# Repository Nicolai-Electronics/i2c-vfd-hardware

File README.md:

# I2C controlled HCS-12SS59T VFD

This repository contains the hardware desgin files for the I2C controlled NE-HCS12SS59T-R01 Vacuum Fluorescent Display board.

## License

Copyright 2024 Nicolai Electronics

This hardware design may be used under the terms of the [CERN-OHL-P](LICENSE) license.

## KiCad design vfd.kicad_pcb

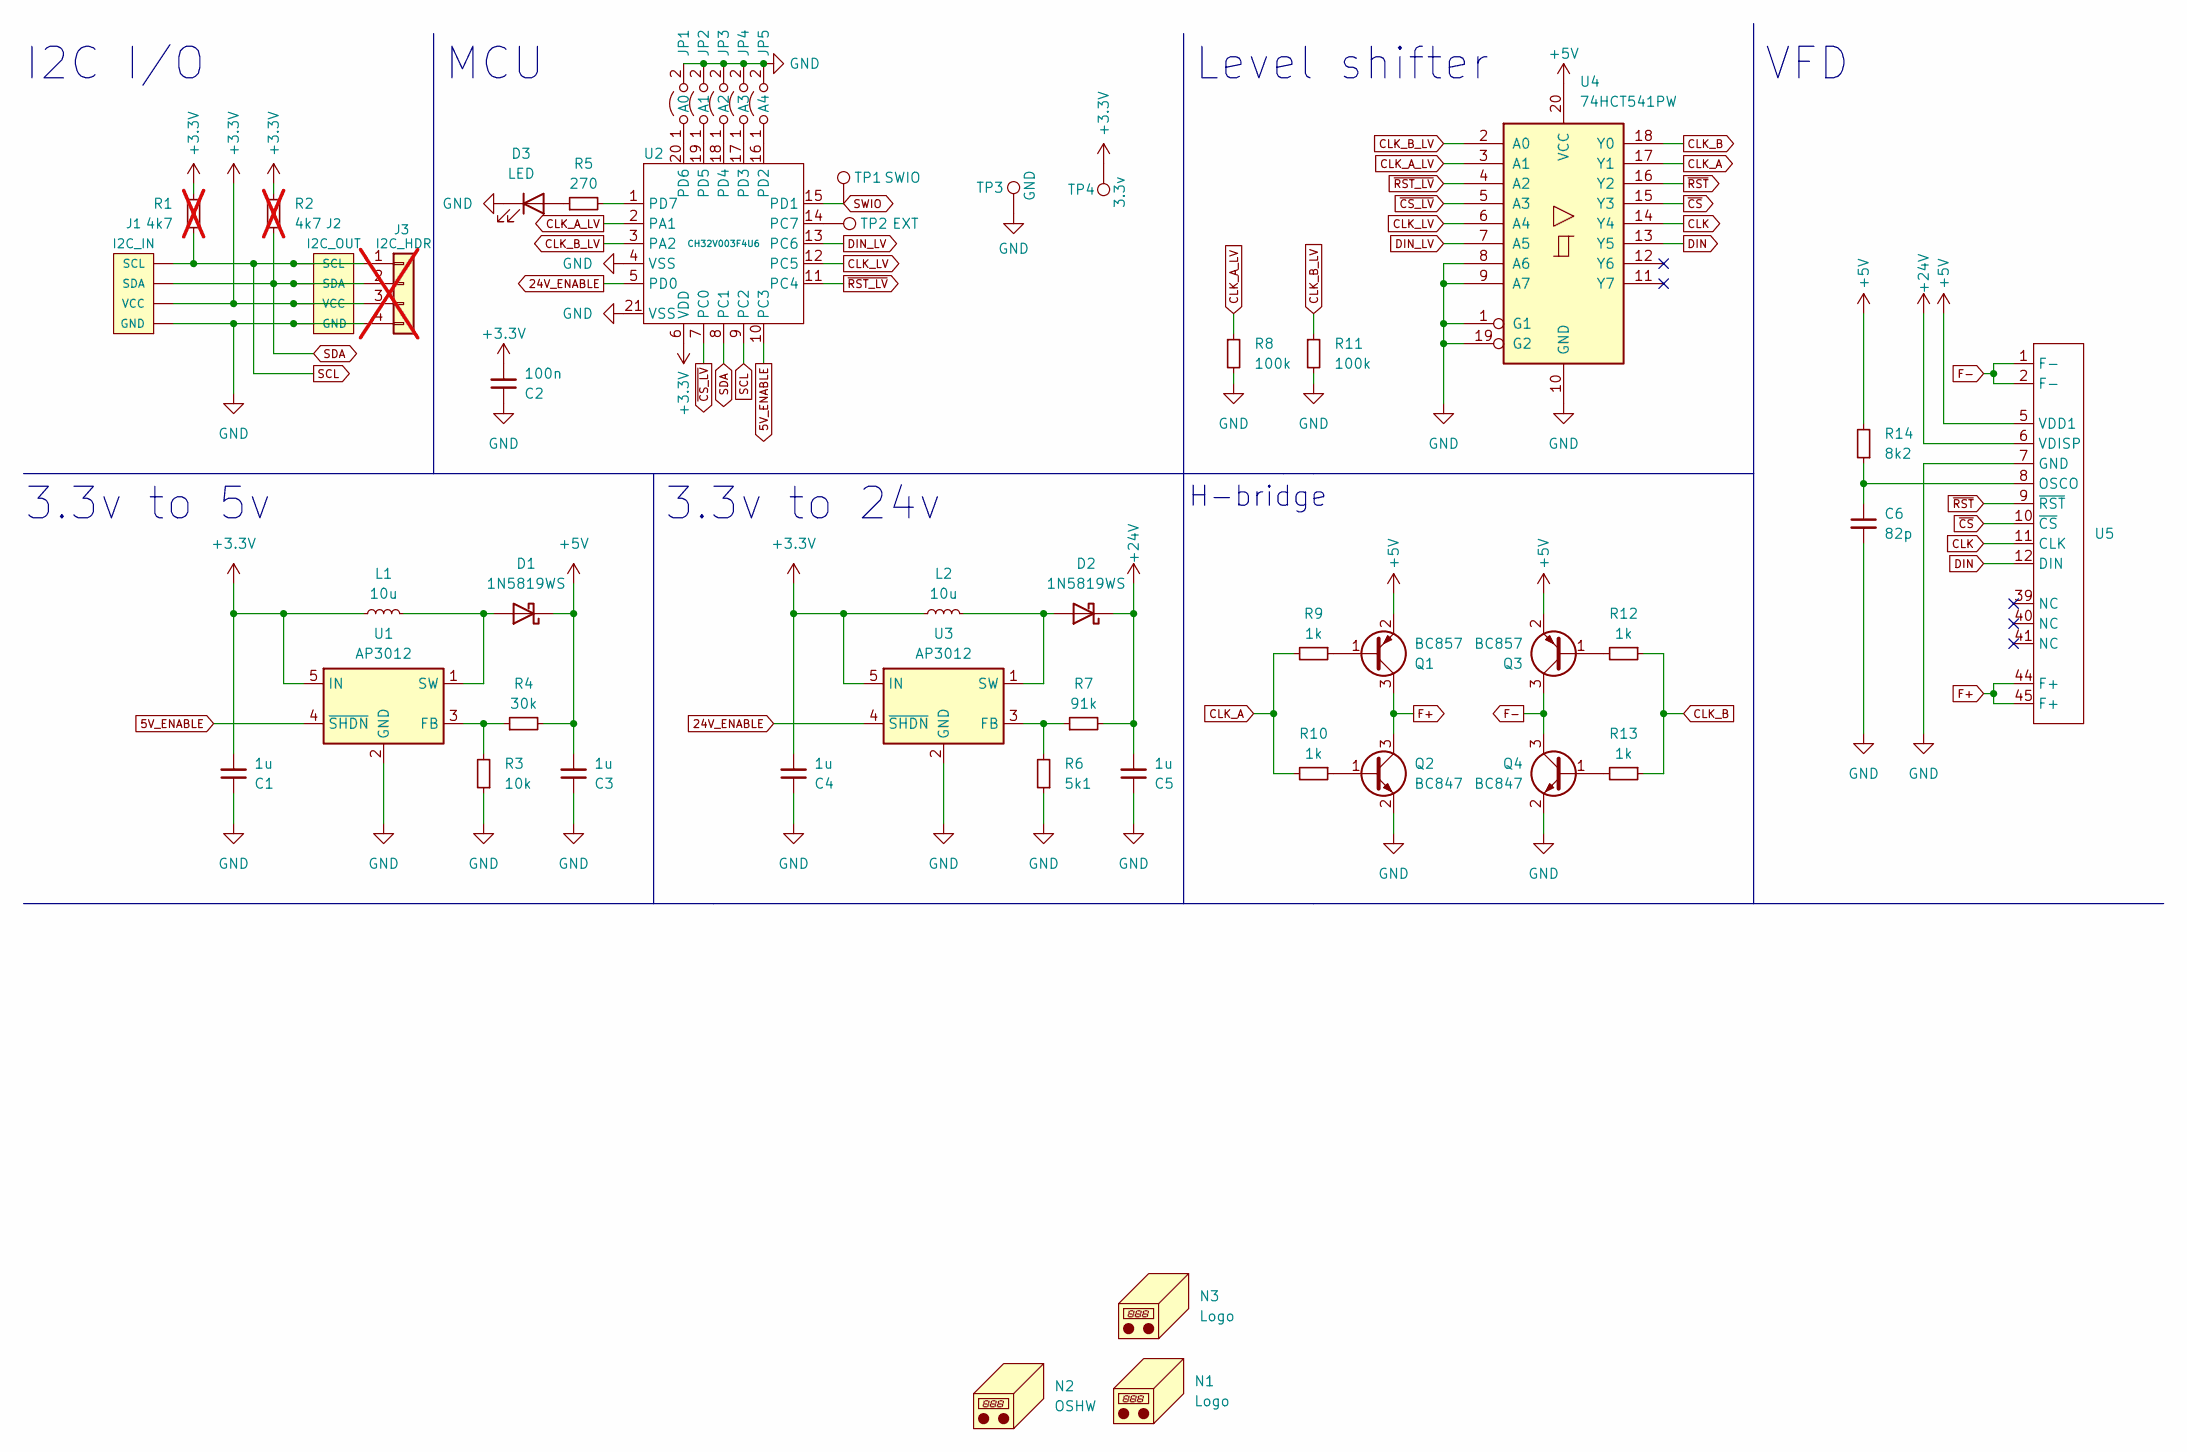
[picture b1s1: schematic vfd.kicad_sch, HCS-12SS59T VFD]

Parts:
C1, C3, C4, C5: 1u; C_0603_1608Metric; LCSC C1592
C2: 100n; C_0603_1608Metric; LCSC C282519
C6: 82p; C_0603_1608Metric; LCSC C1683
D1, D2: 1N5819WS; D_SOD-323; LCSC C191023
D3: LED; LED_0603_1608Metric; LCSC C264473
J1: I2C_IN; 1X04_1MM_RA_GND; LCSC C160404
J2: I2C_OUT; 1X04_1MM_RA_GND; LCSC C160404
J3: I2C_HDR; PinHeader_1x04_P2.54mm_Vertical; not fitted
JP1: A0; SolderJumper-2_P1.3mm_Open_TrianglePad1.0x1.5mm
JP2: A1; SolderJumper-2_P1.3mm_Open_TrianglePad1.0x1.5mm
JP3: A2; SolderJumper-2_P1.3mm_Open_TrianglePad1.0x1.5mm
JP4: A3; SolderJumper-2_P1.3mm_Open_TrianglePad1.0x1.5mm
JP5: A4; SolderJumper-2_P1.3mm_Open_TrianglePad1.0x1.5mm
L1, L2: 10u; Inductor_201610; LCSC C520204
N1, N3: Logo; logo_nicolai
N2: OSHW; OSHW-Logo_5.7x6mm_SilkScreen
Q1, Q3: BC857; SOT-23; LCSC C2139
Q2, Q4: BC847; SOT-23; LCSC C475630
R1, R2: 4k7; R_0603_1608Metric; not fitted
R3: 10k; R_0603_1608Metric; LCSC C25804
R4: 30k; R_0603_1608Metric; LCSC C22984
R5: 270; R_0603_1608Metric; LCSC C22966
R6: 5k1; R_0603_1608Metric; LCSC C23186
R7: 91k; R_0603_1608Metric; LCSC C23265
R8, R11: 100k; R_0603_1608Metric; LCSC C25803
R9, R10, R12, R13: 1k; R_0603_1608Metric; LCSC C21190
R14: 8k2; R_0603_1608Metric; LCSC C25981
TP1: SWIO; TestPoint_Pad_D1.5mm
TP2: EXT; TestPoint_Pad_D1.5mm
TP3: GND; TestPoint_Pad_D1.5mm
TP4: 3.3v; TestPoint_Pad_D1.5mm
U1, U3: AP3012; SOT-23-5; LCSC C102618
U2: CH32V003F4U6; QFN-20-1EP_3x3mm_P0.4mm_EP1.65x1.65mm; LCSC C5299908
U4: 74HCT541PW; TSSOP-20_4.4x6.5mm_P0.65mm; LCSC C131314
U5: HCS-12SS59T

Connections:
5V_ENABLE: U1.4 (~SHDN), U2.10 (PC3)
24V_ENABLE: U2.5 (PD0), U3.4 (~SHDN)
+3.3V: C1.2, C2.2, C4.2, J1.2 (VCC), J2.2 (VCC), J3.3, L1.1, L2.1, R1.2, R2.2, TP4.1, U1.5 (IN), U2.6 (VDD), U3.5 (IN)
+5V: C3.2, D1.1 (K), Q1.2 (E), Q3.2 (E), R4.2, R14.2, U4.20 (VCC), U5.5 (VDD1)
+24V: C5.2, D2.1 (K), R7.2, U5.6 (VDISP)
CLK: U4.14 (Y4), U5.11 (CLK)
CLK_A: R9.2, R10.2, U4.17 (Y1)
CLK_A_LV: R8.1, U2.2 (PA1), U4.3 (A1)
CLK_B: R12.1, R13.1, U4.18 (Y0)
CLK_B_LV: R11.1, U2.3 (PA2), U4.2 (A0)
CLK_LV: U2.12 (PC5), U4.6 (A4)
DIN: U4.13 (Y5), U5.12 (DIN)
DIN_LV: U2.13 (PC6), U4.7 (A5)
F+: Q1.3 (C), Q2.3 (C), U5.44 (F+), U5.45 (F+)
F-: Q3.3 (C), Q4.3 (C), U5.1 (F-), U5.2 (F-)
GND: C1.1, C2.1, C3.1, C4.1, C5.1, C6.2, D3.1 (K), J1.1 (GND), J1.5, J1.6, J2.1 (GND), J2.5, J2.6, J3.4, JP1.2 (B), JP2.2 (B), JP3.2 (B), JP4.2 (B), JP5.2 (B), Q2.2 (E), Q4.2 (E), R3.1, R6.1, R8.2, R11.2, TP3.1, U1.2 (GND), U2.4 (VSS), U2.21 (VSS), U3.2 (GND), U4.1 (G1), U4.8 (A6), U4.9 (A7), U4.10 (GND), U4.19 (G2), U5.7 (GND)
unnamed: D1.2 (A), L1.2, U1.1 (SW)
unnamed: D2.2 (A), L2.2, U3.1 (SW)
unnamed: D3.2 (A), R5.1
unnamed: JP1.1 (A), U2.20 (PD6)
unnamed: JP2.1 (A), U2.19 (PD5)
unnamed: JP3.1 (A), U2.18 (PD4)
unnamed: JP4.1 (A), U2.17 (PD3)
unnamed: JP5.1 (A), U2.16 (PD2)
unnamed: Q1.1 (B), R9.1
unnamed: Q2.1 (B), R10.1
unnamed: Q3.1 (B), R12.2
unnamed: Q4.1 (B), R13.2
unnamed: R3.2, R4.1, U1.3 (FB)
unnamed: TP2.1, U2.14 (PC7)
unnamed: R5.2, U2.1 (PD7)
unnamed: R6.2, R7.1, U3.3 (FB)
unnamed: C6.1, R14.1, U5.8 (OSCO)
SCL: J1.4 (SCL), J2.4 (SCL), J3.1, R1.1, U2.9 (PC2)
SDA: J1.3 (SDA), J2.3 (SDA), J3.2, R2.1, U2.8 (PC1)
SWIO: TP1.1, U2.15 (PD1)
~CS_LV: U2.7 (PC0), U4.5 (A3)
~CS: U4.15 (Y3), U5.10 (~CS)
~RST_LV: U2.11 (PC4), U4.4 (A2)
~RST: U4.16 (Y2), U5.9 (~RST)

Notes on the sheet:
3.3v to 5v
H-bridge
3.3v to 24v
MCU
I2C I/O
VFD
Level shifter

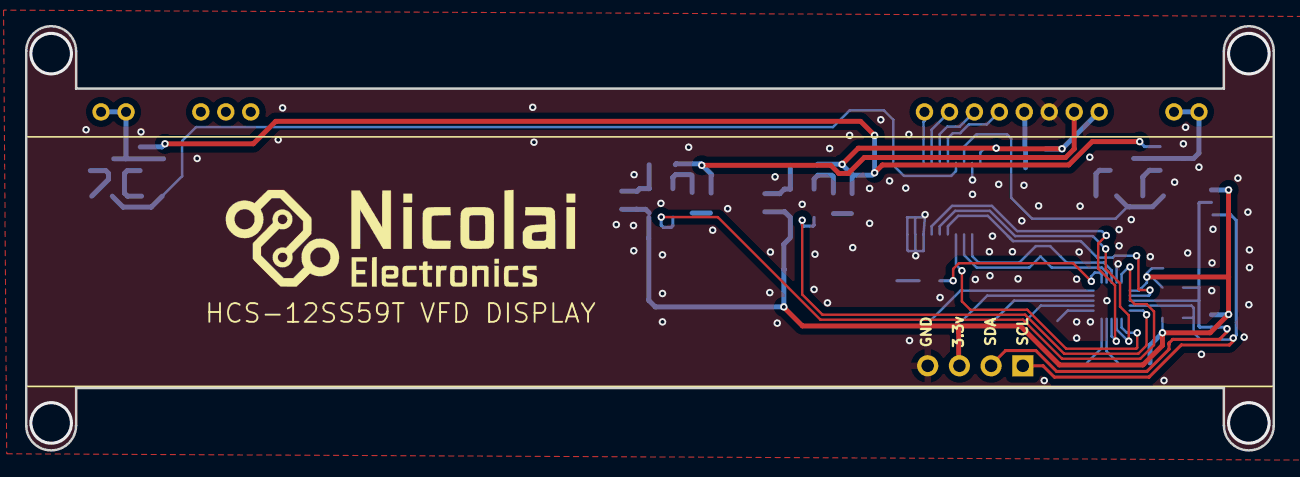
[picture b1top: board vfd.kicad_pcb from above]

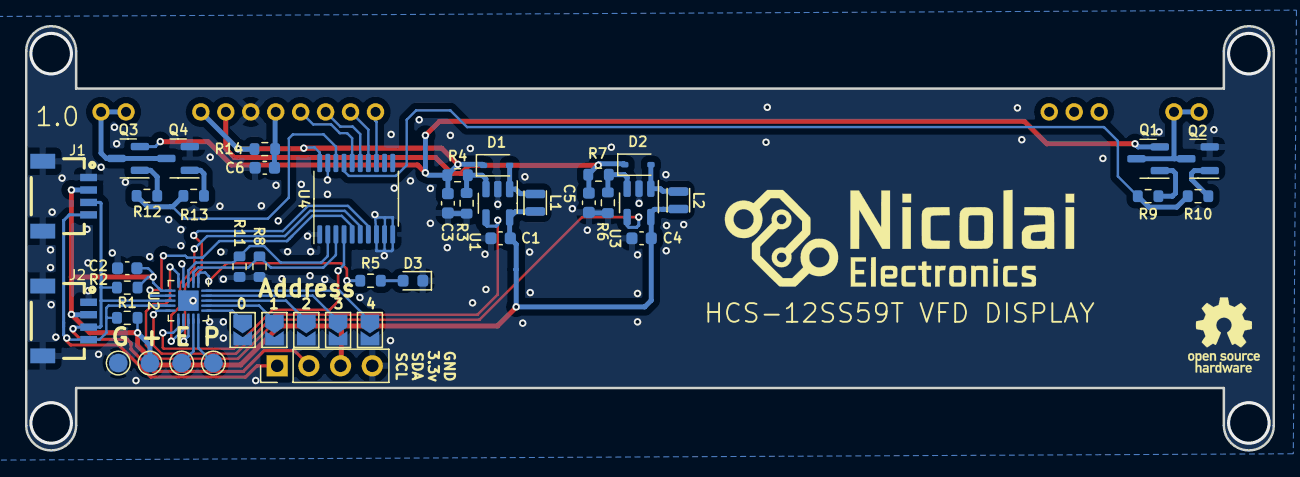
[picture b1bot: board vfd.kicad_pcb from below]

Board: 2 copper layers, 100.0 x 34.0 mm, 49 parts (47 on the bottom side), 40 nets.

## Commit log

2023-08-03 v0.2
2023-09-20 Version 0.2 final
2023-09-20 Add readme and license
2023-09-20 Add PDF schematic
2024-01-23 Make inductor pads bigger, make vfd pads and holes larger
2024-02-26 Revision 1.0 final
2024-02-26 Remove old schematic pdf
2024-03-01 Update copyright notice
